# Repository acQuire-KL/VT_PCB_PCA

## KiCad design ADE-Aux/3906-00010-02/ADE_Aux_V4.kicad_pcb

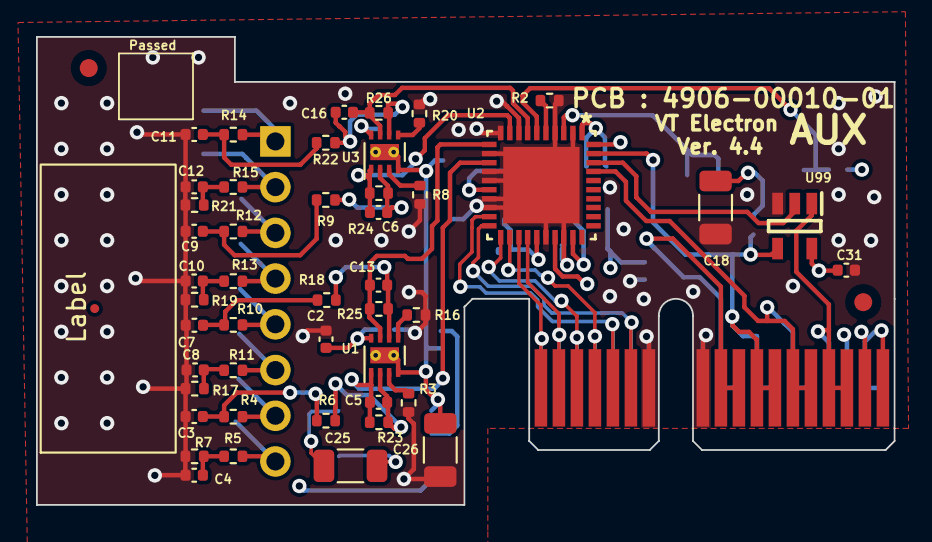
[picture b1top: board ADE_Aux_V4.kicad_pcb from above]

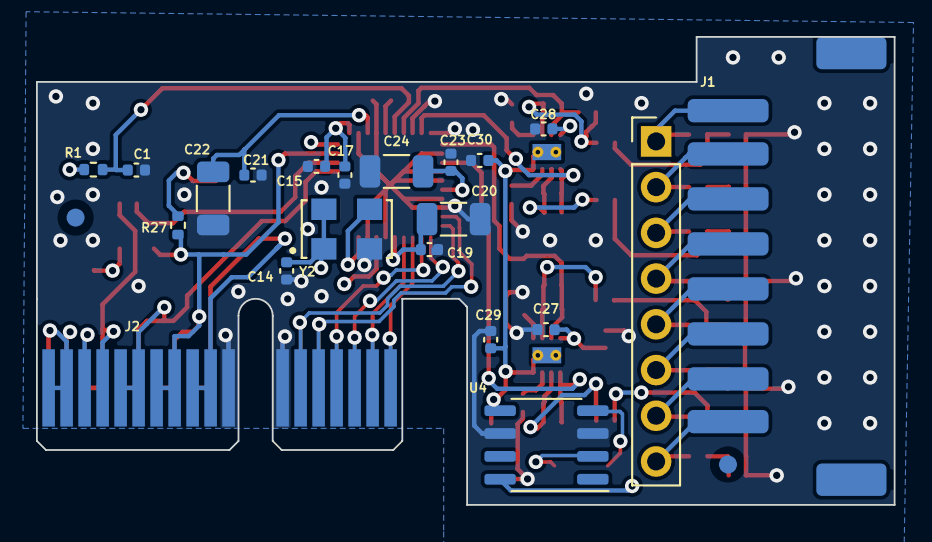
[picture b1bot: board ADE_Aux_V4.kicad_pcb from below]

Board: 4 copper layers, 47.6 x 26.0 mm, 72 parts (23 on the bottom side), 50 nets.

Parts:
C1, C3, C7, C9, C11: 22n; C_0402_1005Metric
C2, C5, C6, C13, C14, C15, C16, C17, C19, C21, C23, C27, C28, C29, C30, C31: 100n; C_0402_1005Metric
C4, C8, C10, C12: DNP; C_0402_1005Metric
C18, C20, C22, C24, C25, C26: 10u; C_1206_3216Metric
FID1, FID2, FID3, FID4: Fiducial; Fiducial_1mm_Mask2mm
J1: MUAS100-8-C-E; A2501-SR08-XH8AWB
J2: Bus_PCI_Express_x1_MOD; BUS_PCIexpress_x1
J15: MUAS100-8-C-E; PinHeader_1x08_P2.54mm_Vertical
R1, R2: 1k; R_0402_1005Metric
R3, R5, R7, R8, R11, R13, R15, R16, R17, R19, R20, R21: 0; R_0402_1005Metric
R4, R10, R12, R14: 100; R_0402_1005Metric
R6, R9, R18, R22, R27: 30K; R_0402_1005Metric
R23, R24, R25, R26: 137K; R_0402_1005Metric
TP1: Eticheta
U1, U3: TLV2186IDSGR; WSON-8-1EP_2x2mm_P0.5mm_EP0.9x1.6mm_ThermalVias
U2: ADE9430
U4: MC7660DR2; SO-8_3.9x4.9mm_P1.27mm
U99: NC7SZ126M5X; Buffer3S
Y2: ECS-5032MV-245.7-BN-TR; OSC_ECS-5032MV-245.7-BN-TR

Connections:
+3V3: C2.1, C14.1, C15.1, C17.1, C18.1, C27.2, C28.2, C31.2, J2.A1, J2.A2, J2.B1, J2.B2, R1.2, R27.1, U1.8 (V+), U2.1 (PullHigh), U2.27 (VDD), U3.8 (V+), U4.8 (V+), U99.5 (VCC), Y2.1 (TRI-STATE), Y2.4 (VDD)
/ADE_Reset: C1.1, J2.B3, R1.1, U2.6 (RESET)
/AVDDOUT: C19.1, C20.1, U2.25 (AVDDOUT)
/C+: C25.1, U4.2 (CAP+)
/C-: C25.2, U4.4 (CAP-)
/DVDDOUT: C21.1, C22.1, U2.3 (DVDDOUT)
/INP: C5.1, R23.1, U1.1, U2.13 (INP)
/IRP: C16.1, R26.1, U2.7 (IAP), U3.7
/ISP: C6.1, R24.1, U2.9 (IBP), U3.1
/ITP: C13.1, R25.1, U1.7, U2.11 (ICP)
/MISO: U2.38 (MISO), U99.2 (A)
/MOSI: J2.A7, J2.A8, J2.B7, J2.B8, R27.2, U2.39 (MOSI), U99.4 (Y)
/O_IN: U2.29 (CLKIN), Y2.3 (OUTPUT)
/PM1: R2.2, U2.5 (PM1)
/REF: C23.1, C24.1, U2.16 (REF)
/RN: C3.1, R4.1, R6.2
/RNM: J1.8, J15.8, R5.2
/RNP: J1.7, J15.7, R4.2
/RR: C11.1, R14.1, R22.2
/RRM: J1.2, J15.2, R15.2
/RRP: J1.1, J15.1, R14.2
/RS: C9.1, R9.2, R12.1
/RSM: J1.4, J15.4, R13.2
/RSP: J1.3, J15.3, R12.2
/RT: C7.1, R10.1, R18.2
/RTM: J1.6, J15.6, R11.2
/RTP: J1.5, J15.5, R10.2
/SCLK: J2.A5, J2.A6, J2.B5, J2.B6, U2.37 (SCLK)
/SS: J2.A9, J2.A10, J2.B9, J2.B10, U2.40 (SS)
/SYN: J2.A3, J2.A4, J2.B4, U99.1 (OE)
/UM: C26.2, C29.2, C30.2, U1.4 (V-), U1.9 (PAD), U3.4 (V-), U3.9 (PAD), U4.5 (VOUT)
/UR+: J2.A14, J2.B14, U2.19 (VAN)
/UR-: J2.A13, J2.B13, U2.20 (VAP)
/US+: J2.A16, J2.B16, U2.21 (VBN)
/US-: J2.A15, J2.B15, U2.22 (VBP)
/UT+: J2.A18, J2.B18, U2.23 (VCN)
/UT-: J2.A17, J2.B17, U2.24 (VCP)
GND: C1.2, C2.2, C3.2, C4.2, C7.2, C8.2, C9.2, C10.2, C11.2, C12.2, C14.2, C15.2, C17.2, C18.2, C19.2, C20.2, C21.2, C22.2, C23.2, C24.2, C26.1, C27.1, C28.1, C29.1, C30.1, C31.1, J2.A11, J2.A12, J2.B11, J2.B12, R2.1, R3.2, R7.2, R8.2, R16.2, R17.2, R19.2, R20.2, R21.2, U2.2 (DGND), U2.4 (PM0), U2.8 (IAN), U2.10 (IBN), U2.12 (ICN), U2.14 (INN), U2.15 (REFGND), U2.17 (NC1), U2.18 (NC2), U2.26 (AGND), U2.28 (GND), U2.41 (EP), U4.3 (GND), U4.6 (LV), U99.3 (GND), Y2.2 (GND)
unnamed: C4.1, R5.1, R7.1
unnamed: C8.1, R11.1, R17.1
unnamed: C10.1, R13.1, R19.1
unnamed: C12.1, R15.1, R21.1
unnamed: R3.1, U1.3 (+)
unnamed: C5.2, R6.1, R23.2, U1.2 (-)
unnamed: R16.1, U1.5 (+)
unnamed: C13.2, R18.1, R25.2, U1.6 (-)
unnamed: R8.1, U3.3 (+)
unnamed: C6.2, R9.1, R24.2, U3.2 (-)
unnamed: R20.1, U3.5 (+)
unnamed: C16.2, R22.1, R26.2, U3.6 (-)

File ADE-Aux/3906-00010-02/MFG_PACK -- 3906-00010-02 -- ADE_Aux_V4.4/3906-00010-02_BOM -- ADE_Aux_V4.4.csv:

"Reference","VTPN","Value","Datasheet","Footprint","Qty","DNP"
"FID1,FID2,FID3,FID4","4000-00000-00","Fiducial","~","Fiducial:Fiducial_1mm_Mask2mm","4","DNP"
"J2","4000-00000-00","Bus_PCI_Express_x1_MOD","http://www.ritrontek.com/uploadfile/2016/1026/20161026105231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","Connector_PCBEdge:BUS_PCIexpress_x1","1","DNP"
"J15","4000-00000-00","MUAS100-8-C-E","~","Connector_PinHeader_2.54mm:PinHeader_1x08_P2.54mm_Vertical","1","DNP"
"TP1","4000-00000-00","Eticheta","~","Symbol:Eticheta","1","DNP"
"C4,C8,C10,C12","4004-00000-00","DNP","~","Capacitor_SMD:C_0402_1005Metric","4",""
"R3,R5,R7,R8,R11,R13,R15,R16,R17,R19,R20,R21","4004-00001-00","0","~","Resistor_SMD:R_0402_1005Metric","12",""
"R1,R2","4004-00010-00","1k","~","Resistor_SMD:R_0402_1005Metric","2",""
"R4,R10,R12,R14","4004-00020-00","100","~","Resistor_SMD:R_0402_1005Metric","4",""
"R6,R9,R18,R22,R27","4004-00100-00","30K","~","Resistor_SMD:R_0402_1005Metric","5",""
"R23,R24,R25,R26","4004-02000-00","137K","~","Resistor_SMD:R_0402_1005Metric","4",""
"C1,C3,C7,C9,C11","4104-00020-00","22n","~","Capacitor_SMD:C_0402_1005Metric","5",""
"C2,C5,C6,C13,C14,C15,C16,C17,C19,C21,C23,C27,C28,C29,C30,C31","4104-00100-00","100n","~","Capacitor_SMD:C_0402_1005Metric","16",""
"C18,C20,C22,C24,C25,C26","4112-00100-00","10u","~","Capacitor_SMD:C_1206_3216Metric","6",""
"J1","4408-00010-00","MUAS100-8-C-E","~","Connector_JST:A2501-SR08-XH8AWB","1",""
"U4","4520-00030-00","MC7660DR2","http://www.ti.com/lit/ds/symlink/lmc7660.pdf","Package_SO:SO-8_3.9x4.9mm_P1.27mm","1",""
"U2","4706-00030-00","ADE9430","","Package_QFP:ADE9430","1",""
"U1,U3","4708-00010-00","TLV2186IDSGR","-- mixed values --","Package_SON:WSON-8-1EP_2x2mm_P0.5mm_EP0.9x1.6mm_ThermalVias","2",""
"Y2","4712-00020-00","ECS-5032MV-245.7-BN-TR","","Oscillator:OSC_ECS-5032MV-245.7-BN-TR","1",""
"U99","4726-00010-00","NC7SZ126M5X","","Buffer3S:Buffer3S","1",""

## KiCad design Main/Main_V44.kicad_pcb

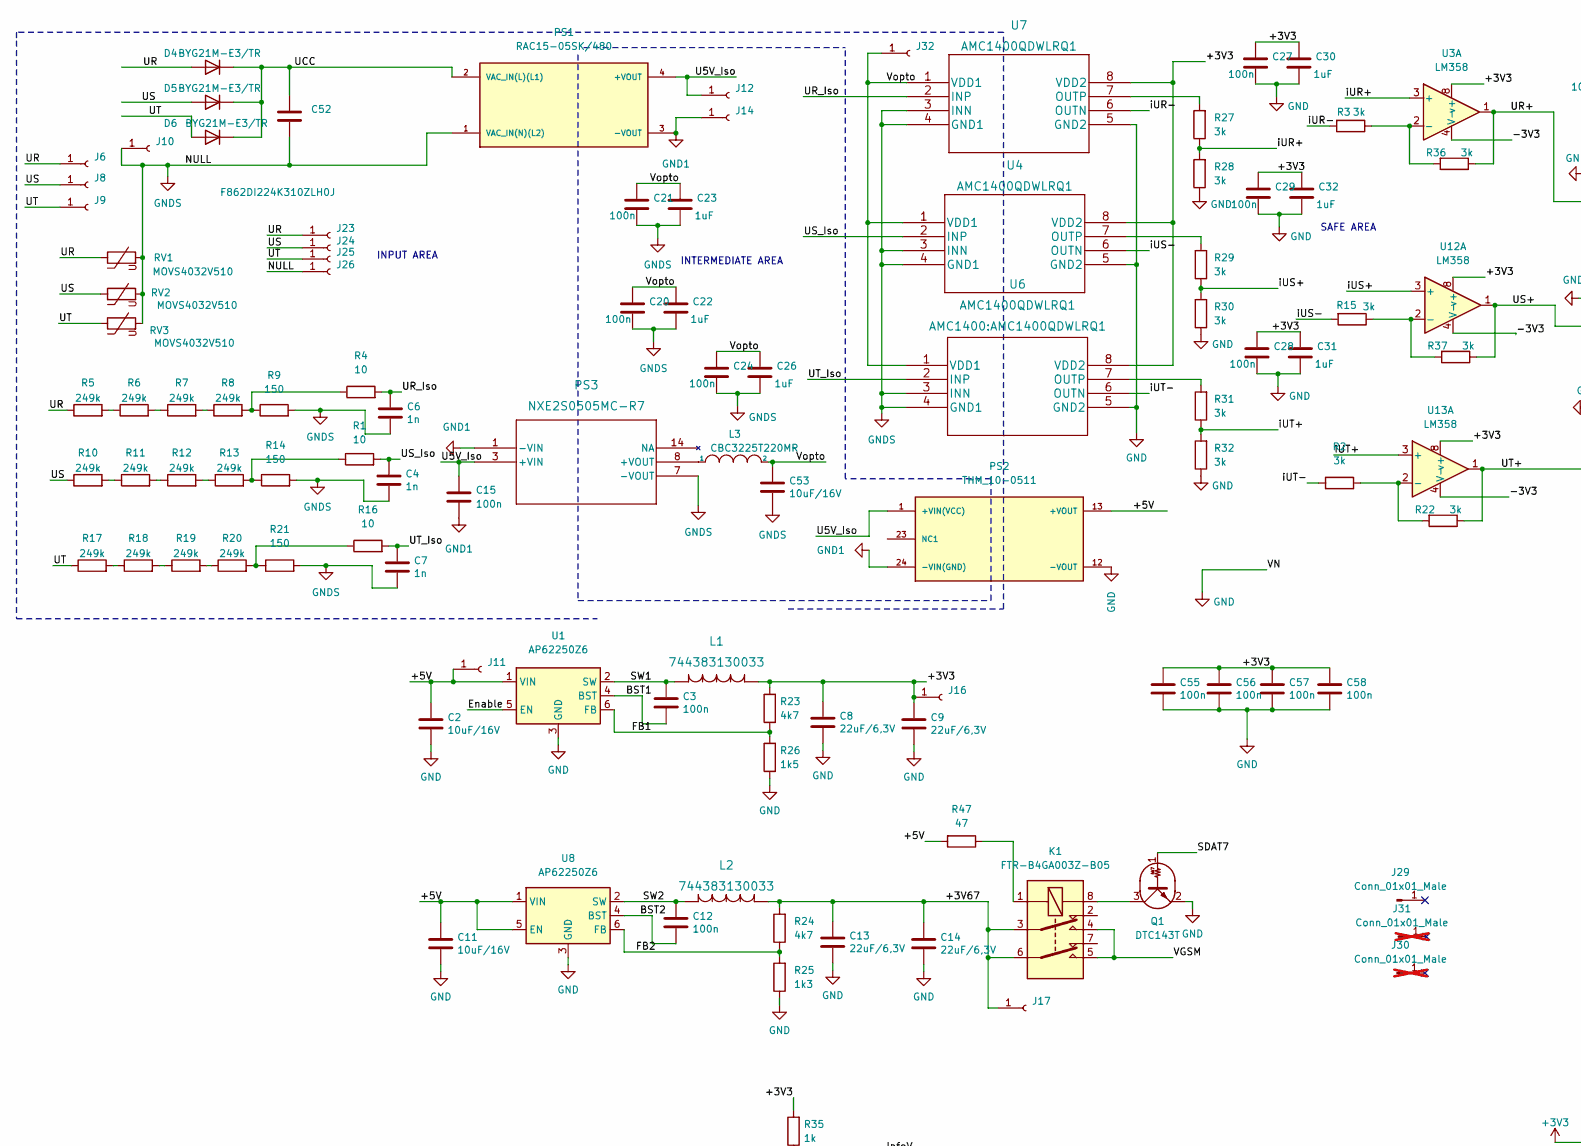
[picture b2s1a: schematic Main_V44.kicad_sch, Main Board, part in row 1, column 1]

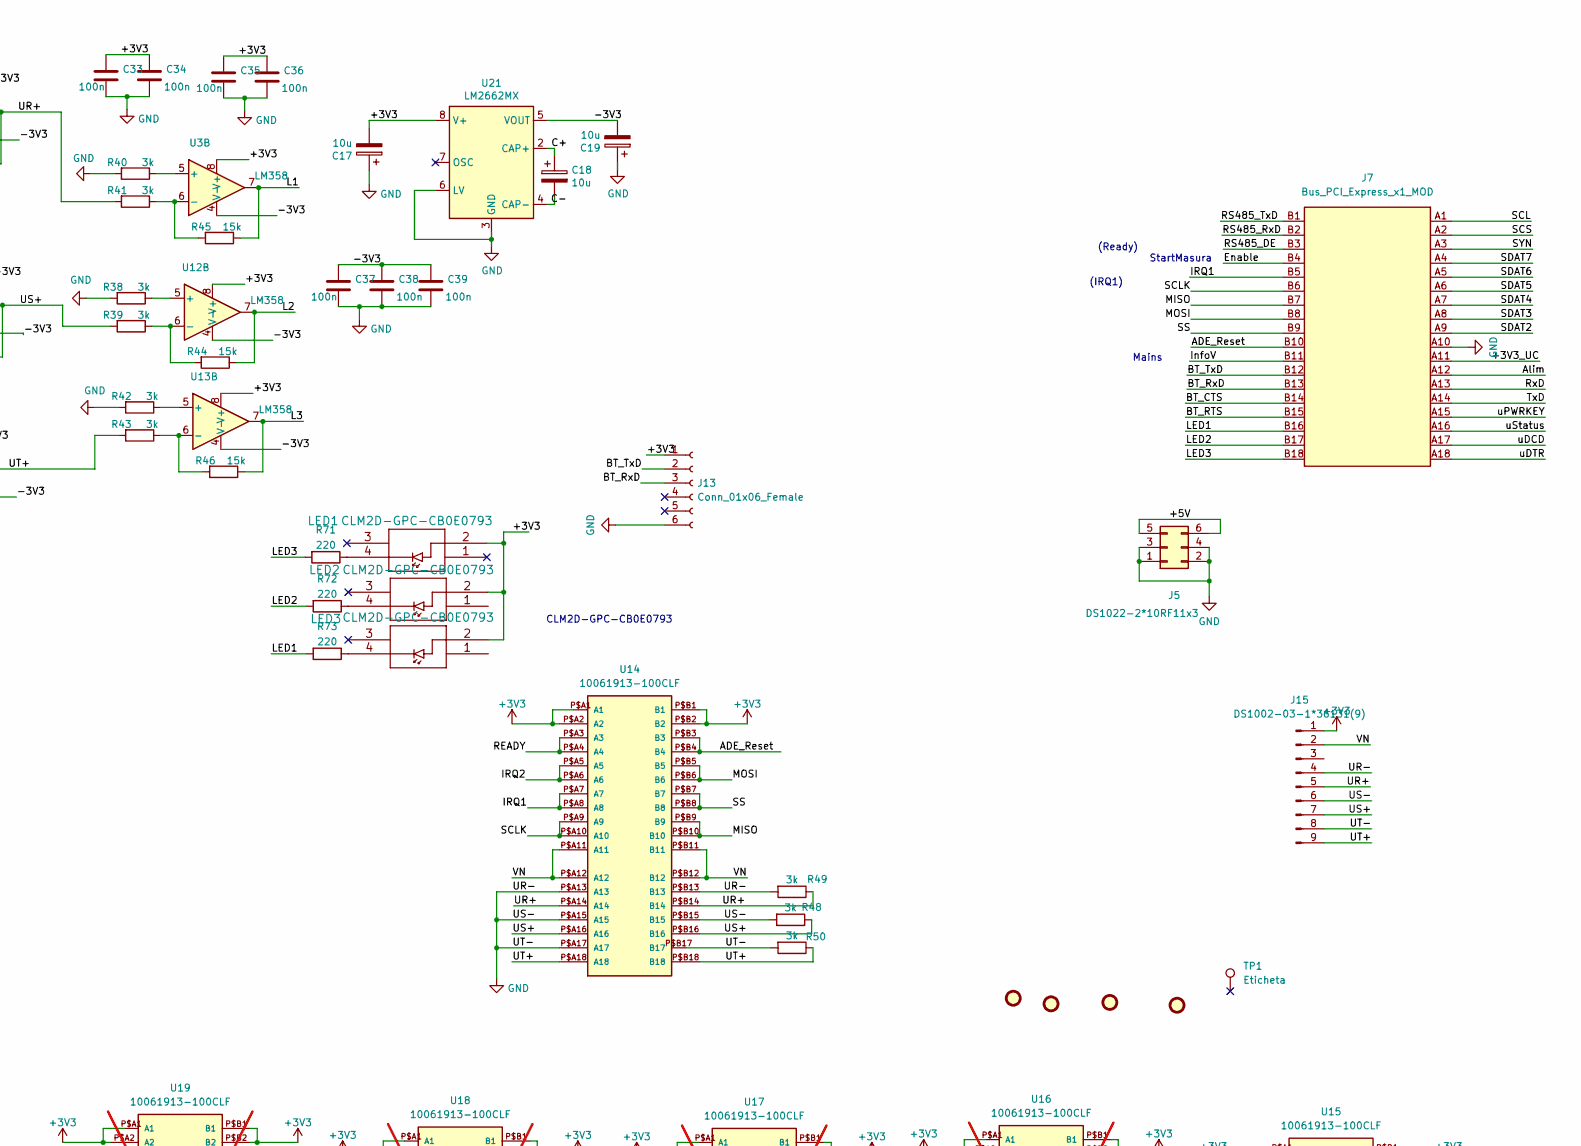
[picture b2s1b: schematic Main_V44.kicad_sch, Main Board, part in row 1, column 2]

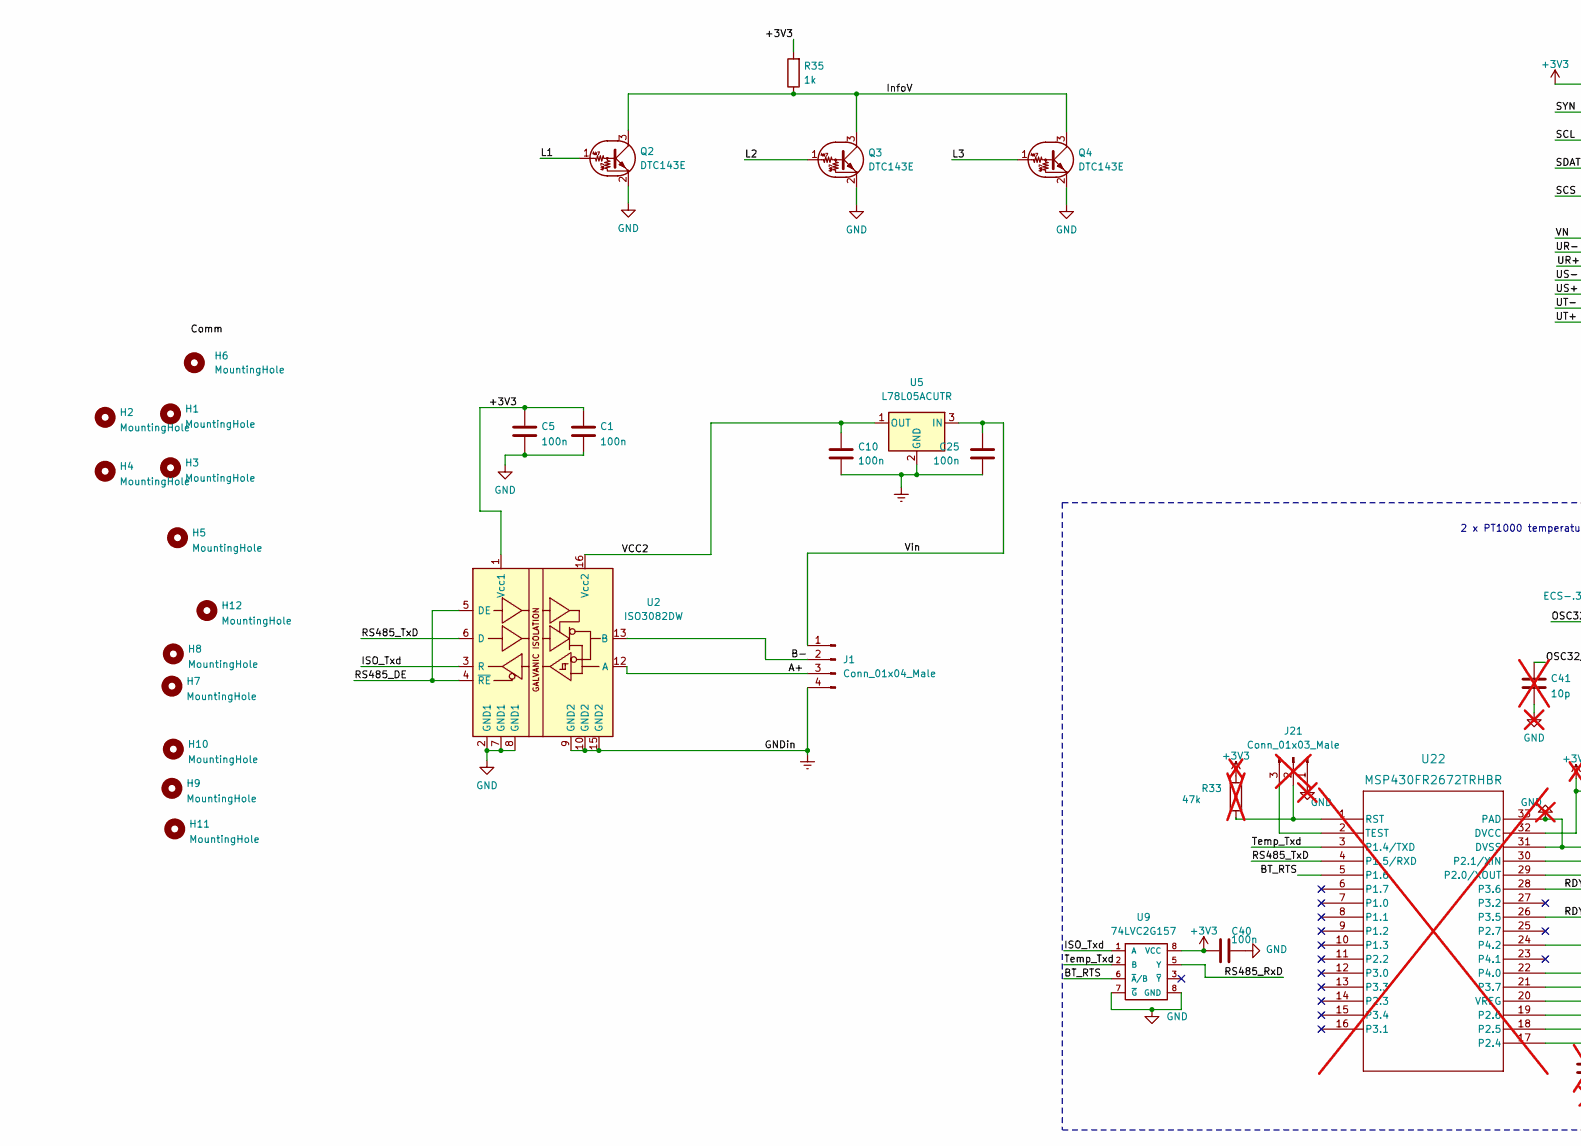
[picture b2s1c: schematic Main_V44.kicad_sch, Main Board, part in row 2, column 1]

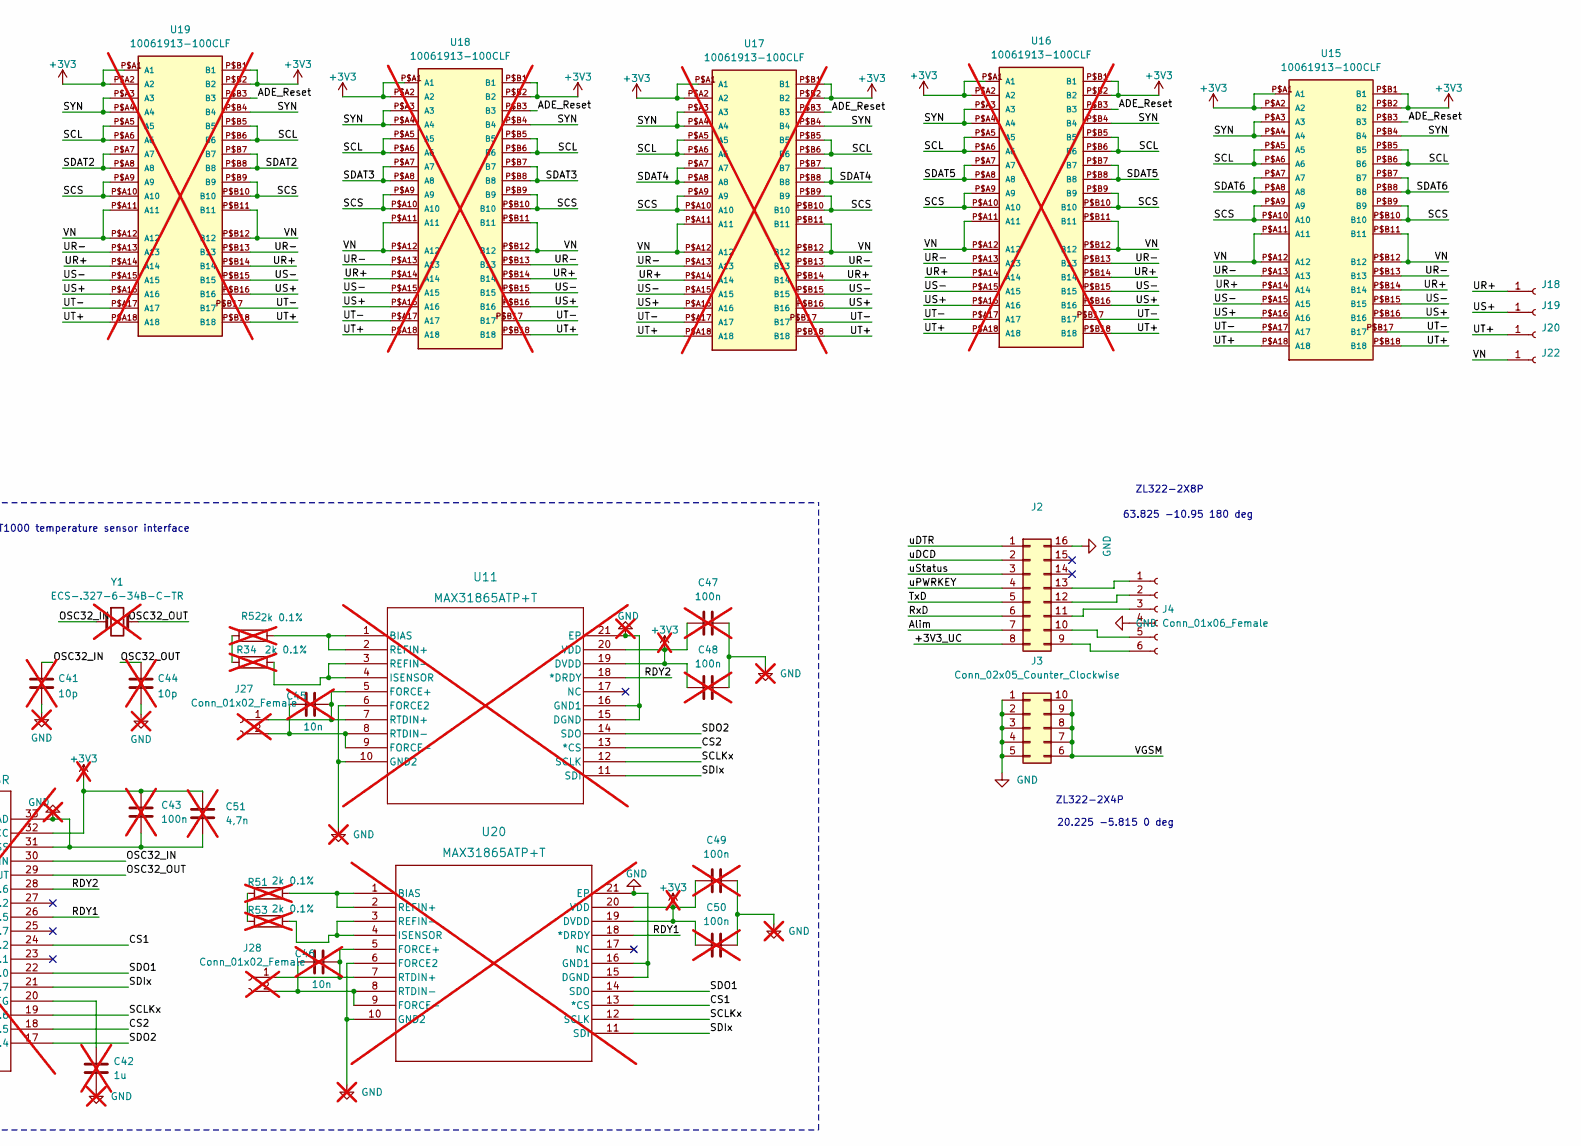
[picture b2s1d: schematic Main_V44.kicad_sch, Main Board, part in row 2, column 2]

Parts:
C1, C3, C5, C10, C12, C15, C20, C21, C24, C25, C27, C28, C29, C33, C34, C35, C36, C37, C38, C39, C40, C55, C56, C57, C58: 100n; C_0603_1608Metric
C2, C11, C53: 10uF/16V; C_1206_3216Metric
C4, C6, C7: 1n; C_0603_1608Metric
C8, C9, C13, C14: 22uF/6,3V; C_1206_3216Metric
C17, C18, C19: 10u; C_1206_3216Metric
C22, C23, C26, C30, C31, C32: 1uF; C_0603_1608Metric
C41, C44: 10p; C_0603_1608Metric; not fitted
C42: 1u; C_0603_1608Metric; not fitted
C43, C47, C48, C49, C50: 100n; C_0603_1608Metric; not fitted
C45, C46: 10n; C_0603_1608Metric; not fitted
C51: 4,7n; C_0603_1608Metric; not fitted
C52: F862DI224K310ZLH0J; C_Rect_L24.0mm_W7.0mm_P22.50mm_MKT
D4, D5, D6: BYG21M-E3/TR; D_SMA
FID1, FID2, FID3, FID4: Fiducial; Fiducial_1mm_Mask2mm
H1, H6: MountingHole; MountingHole_3.2mm_M3_ISO14580_Pad_TopBottom
H2, H3, H4, H5, H7, H8, H9, H10, H11, H12: MountingHole; MountingHole_3.2mm_M3
J1: Conn_01x04_Male; A2501-SR04-XH4AWB
J2: Conn_02x08_Counter_Clockwise; PinSocket_2x08_P2.54mm_Vertical_SMD_MOD
J3: Conn_02x05_Counter_Clockwise; PinSocket_2x05_P2.54mm_Vertical_SMD
J4, J13: Conn_01x06_Female; PinSocket_1x06_P2.54mm_Vertical
J5: DS1022-2*10RF11x3; PinHeader_2x03_P2.54mm_Horizontal
J6, J8, J9, J10, J11, J12, J14, J16, J17, J18, J19, J20, J22, J32: Conn_01x01_Female; TestPoint_DELTA
J7: Bus_PCI_Express_x1_MOD; BUS_PCIexpress_x1
J15: DS1002-03-1*36131(9); PinSocket_1x09_P2.54mm_Vertical
J21: Conn_01x03_Male; PinHeader_1x03_P2.54mm_Vertical; not fitted
J23: Conn_01x01_Female; DELTA_SolderWire-1.5sqmm_1x01_D1.7mm_OD3.9mm
J24, J25, J26: Conn_01x01_Female; DELTA_R_SolderWire-1.5sqmm_1x01_D1.7mm_OD3.9mm
J27, J28: Conn_01x02_Female; TerminalBlock_bornier-2_P5.08mm; not fitted
J29: Conn_01x01_Male; TestPoint_Pad_5.1x5.1mm
J30, J31: Conn_01x01_Male; TestPoint_Pad_5.1x5.1mm; not fitted
K1: FTR-B4GA003Z-B05; Relay_Fujitsu_FTR-B4GA003
L1, L2: 744383130033
L3: CBC3225T220MR; L_1206_3216Metric
LED1, LED2, LED3: CLM2D-GPC-CB0E0793
PS1: RAC15-05SK/480; CONV_RAC15-12SK_480; PARTREV 0/2022
PS2: THM_10-0511; CONV_THM_10-0511; PARTREV Jan 06, 2021
PS3: NXE2S0505MC-R7; NXE2_SINGLE_SURFACE_MUR
Q1: DTC143T; SOT-23
Q2, Q3, Q4: DTC143E; SOT-23
R1, R4, R16: 10; R_0603_1608Metric
R2, R3, R15, R22, R27, R28, R29, R30, R31, R32, R36, R37, R38, R39, R40, R41, R42, R43, R48, R49, R50: 3k; R_0603_1608Metric
R5, R6, R7, R8, R10, R11, R12, R13, R17, R18, R19, R20: 249k; R_2512_6332Metric
R9, R14, R21: 150; R_0603_1608Metric
R23, R24: 4k7; R_0603_1608Metric
R25: 1k3; R_0603_1608Metric
R26: 1k5; R_0603_1608Metric
R33: 47k; R_0603_1608Metric; not fitted
R34, R51, R52, R53: 2k 0.1%; R_0603_1608Metric; not fitted
R35: 1k; R_0603_1608Metric
R44, R45, R46: 15k; R_0603_1608Metric
R47: 47; R_0603_1608Metric
R71, R72, R73: 220; R_0603_1608Metric
RV1, RV2, RV3: MOVS4032V510; MOVS4032V460
TP1: Eticheta
U1, U8: AP62250Z6; SOT-563
U2: ISO3082DW; SOIC-16W_7.5x10.3mm_P1.27mm
U3, U12, U13: LM358; SO-8_3.9x4.9mm_P1.27mm
U4, U6, U7: AMC1400QDWLRQ1
U5: L78L05ACUTR; SOT-89-3
U9: 74LVC2G157; VSSOP-8_2.4x2.1mm_P0.5mm
U11, U20: MAX31865ATP+T; 21-0140L_T2055-5_MXM; not fitted
U14, U15: 10061913-100CLF; MPN 10061913-100CLF
U16, U17, U18, U19: 10061913-100CLF; MPN 10061913-100CLF; not fitted
U21: LM2662MX; SO-8_3.9x4.9mm_P1.27mm
U22: MSP430FR2672TRHBR; VQFN32_5X5_TEX; not fitted
Y1: ECS-.327-6-34B-C-TR; Crystal_SMD_EuroQuartz_EQ161-2Pin_3.2x1.5mm; not fitted

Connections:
/+3V3_UC: J2.8, J7.A11
/+3V67: C13.1, C14.1, J17.1, K1.3, K1.6, L2.1, R24.2
/+5V: C2.1, C11.1, J5.5, J5.6, J11.1, PS2.13 (+VOUT), R47.2, U1.1 (VIN), U8.1 (VIN), U8.5 (EN)
/-3V3: C19.2, C37.1, C38.1, C39.1, U3.4 (V-), U12.4 (V-), U13.4 (V-), U21.5 (VOUT)
/A+: J1.3, U2.12 (A)
/ADE_Reset: J7.B10, U14.P$B3 (B3), U14.P$B4 (B4), U15.P$B3 (B3), U16.P$B3 (B3), U17.P$B3 (B3), U18.P$B3 (B3), U19.P$B3 (B3)
/Alim: J2.7, J7.A12
/B-: J1.2, U2.13 (B)
/BST1: C3.2, U1.4 (BST)
/BST2: C12.2, U8.4 (BST)
/BT_CTS: J7.B14
/BT_RTS: J7.B15, U9.6 (~A/B), U22.5 (P1.6)
/BT_RxD: J7.B13, J13.3
/BT_TxD: J7.B12, J13.2
/C+: C18.1, U21.2 (CAP+)
/C-: C18.2, U21.4 (CAP-)
/CS1: U20.13 (*CS), U22.24 (P4.2)
/CS2: U11.13 (*CS), U22.18 (P2.5)
/Enable: J7.B4, U1.5 (EN)
/FB1: R23.1, R26.2, U1.6 (FB)
/FB2: R24.1, R25.2, U8.6 (FB)
/IRQ1: J7.B5, U14.P$A7 (A7), U14.P$A8 (A8)
/IRQ2: U14.P$A5 (A5), U14.P$A6 (A6)
/ISO_Txd: U2.3 (R), U9.1 (A)
/InfoV: J7.B11, Q2.3 (C), Q3.3 (C), Q4.3 (C), R35.1
/L1: Q2.1 (B), R45.1, U3.7
/L2: Q3.1 (B), R44.1, U12.7
/L3: Q4.1 (B), R46.1, U13.7
/LED1: J7.B16, R73.2
/LED2: J7.B17, R72.2
/LED3: J7.B18, R71.2
/MISO: J7.B7, U14.P$B9 (B9), U14.P$B10 (B10)
/MOSI: J7.B8, U14.P$B5 (B5), U14.P$B6 (B6)
/OSC32_IN: C41.1, U22.30 (P2.1/XIN), Y1.1
/OSC32_OUT: C44.1, U22.29 (P2.0/XOUT), Y1.2
/RDY1: U20.18 (*DRDY), U22.26 (P3.5)
/RDY2: U11.18 (*DRDY), U22.28 (P3.6)
/READY: U14.P$A3 (A3), U14.P$A4 (A4)
/RS485_DE: J7.B3, U2.4 (~RE), U2.5 (DE)
/RS485_RxD: J7.B2, U9.5 (Y)
/RS485_TxD: J7.B1, U2.6 (D), U22.4 (P1.5/RXD)
/RxD: J2.6, J7.A13
/SCL: J7.A1, U15.P$A5 (A5), U15.P$A6 (A6), U15.P$B5 (B5), U15.P$B6 (B6), U16.P$A5 (A5), U16.P$A6 (A6), U16.P$B5 (B5), U16.P$B6 (B6), U17.P$A5 (A5), U17.P$A6 (A6), U17.P$B5 (B5), U17.P$B6 (B6), U18.P$A5 (A5), U18.P$A6 (A6), U18.P$B5 (B5), U18.P$B6 (B6), U19.P$A5 (A5), U19.P$A6 (A6), U19.P$B5 (B5), U19.P$B6 (B6)
/SCLK: J7.B6, U14.P$A9 (A9), U14.P$A10 (A10)
/SCLKx: U11.12 (SCLK), U20.12 (SCLK), U22.19 (P2.6)
/SCS: J7.A2, U15.P$A9 (A9), U15.P$A10 (A10), U15.P$B9 (B9), U15.P$B10 (B10), U16.P$A9 (A9), U16.P$A10 (A10), U16.P$B9 (B9), U16.P$B10 (B10), U17.P$A9 (A9), U17.P$A10 (A10), U17.P$B9 (B9), U17.P$B10 (B10), U18.P$A9 (A9), U18.P$A10 (A10), U18.P$B9 (B9), U18.P$B10 (B10), U19.P$A9 (A9), U19.P$A10 (A10), U19.P$B9 (B9), U19.P$B10 (B10)
/SDAT2: J7.A9, U19.P$A7 (A7), U19.P$A8 (A8), U19.P$B7 (B7), U19.P$B8 (B8)
/SDAT3: J7.A8, U18.P$A7 (A7), U18.P$A8 (A8), U18.P$B7 (B7), U18.P$B8 (B8)
/SDAT4: J7.A7, U17.P$A7 (A7), U17.P$A8 (A8), U17.P$B7 (B7), U17.P$B8 (B8)
/SDAT5: J7.A6, U16.P$A7 (A7), U16.P$A8 (A8), U16.P$B7 (B7), U16.P$B8 (B8)
/SDAT6: J7.A5, U15.P$A7 (A7), U15.P$A8 (A8), U15.P$B7 (B7), U15.P$B8 (B8)
/SDAT7: J7.A4, Q1.1 (B)
/SDIx: U11.11 (SDI), U20.11 (SDI), U22.21 (P3.7)
/SDO1: U20.14 (SDO), U22.22 (P4.0)
/SDO2: U11.14 (SDO), U22.17 (P2.4)
/SS: J7.B9, U14.P$B7 (B7), U14.P$B8 (B8)
/SW1: C3.1, L1.2, U1.2 (SW)
/SW2: C12.1, L2.2, U8.2 (SW)
/SYN: J7.A3, U15.P$A3 (A3), U15.P$A4 (A4), U15.P$B4 (B4), U16.P$A3 (A3), U16.P$A4 (A4), U16.P$B4 (B4), U17.P$A3 (A3), U17.P$A4 (A4), U17.P$B4 (B4), U18.P$A3 (A3), U18.P$A4 (A4), U18.P$B4 (B4), U19.P$A3 (A3), U19.P$A4 (A4), U19.P$B4 (B4)
/Temp_Txd: U9.2 (B), U22.3 (P1.4/TXD)
/TxD: J2.5, J7.A14
/U5V_Iso: C15.1, J12.1, PS1.4 (+VOUT), PS2.1 (+VIN(VCC)), PS3.3 (+VIN)
/UCC: C52.1, D4.1 (K), D5.1 (K), D6.1 (K), PS1.2 (VAC_IN(L)(L1))
/UR: D4.2 (A), J6.1, J23.1, R5.1, RV1.1
/UR+: J15.5, J18.1, R36.1, R41.2, R49.1, U3.1, U14.P$A14 (A14), U14.P$B14 (B14), U15.P$A14 (A14), U15.P$B14 (B14), U16.P$A14 (A14), U16.P$B14 (B14), U17.P$A14 (A14), U17.P$B14 (B14), U18.P$A14 (A14), U18.P$B14 (B14), U19.P$A14 (A14), U19.P$B14 (B14)
/UR_Iso: C6.1, R4.2, U7.2 (INP)
/US: D5.2 (A), J8.1, J24.1, R10.1, RV2.1
/US+: J15.7, J19.1, R37.1, R39.2, R48.1, U12.1, U14.P$A16 (A16), U14.P$B16 (B16), U15.P$A16 (A16), U15.P$B16 (B16), U16.P$A16 (A16), U16.P$B16 (B16), U17.P$A16 (A16), U17.P$B16 (B16), U18.P$A16 (A16), U18.P$B16 (B16), U19.P$A16 (A16), U19.P$B16 (B16)
/US_Iso: C4.1, R1.2, U4.2 (INP)
/UT: D6.2 (A), J9.1, J25.1, R17.1, RV3.1
/UT+: J15.9, J20.1, R22.1, R43.2, R50.1, U13.1, U14.P$A18 (A18), U14.P$B18 (B18), U15.P$A18 (A18), U15.P$B18 (B18), U16.P$A18 (A18), U16.P$B18 (B18), U17.P$A18 (A18), U17.P$B18 (B18), U18.P$A18 (A18), U18.P$B18 (B18), U19.P$A18 (A18), U19.P$B18 (B18)
/UT_Iso: C7.1, R16.2, U6.2 (INP)
/VCC2: C10.1, U2.16 (Vcc2), U5.1 (OUT)
/VGSM: J3.6, J3.7, J3.8, J3.9, J3.10, K1.4, K1.5
/Vin: C25.1, J1.1, U5.3 (IN)
/Vopto: C20.1, C21.1, C22.1, C23.1, C24.1, C26.1, C53.1, J32.1, L3.2, U4.1 (VDD1), U6.1 (VDD1), U7.1 (VDD1)
/iUR+: R27.1, R28.2, U3.3 (+)
/iUR-: R3.2, U7.6 (OUTN)
/iUS+: R29.1, R30.2, U12.3 (+)
/iUS-: R15.2, U4.6 (OUTN)
/iUT+: R31.1, R32.2, U13.3 (+)
/iUT-: R2.2, U6.6 (OUTN)
/uDCD: J2.2, J7.A17
/uDTR: J2.1, J7.A18
/uPWRKEY: J2.4, J7.A15
/uStatus: J2.3, J7.A16
Earth: C10.2, C25.2, J1.4, U2.9 (GND2), U2.10 (GND2), U2.15 (GND2), U5.2 (GND)
GND1: C15.2, J14.1, PS1.3 (-VOUT), PS2.24 (-VIN(GND)), PS3.1 (-VIN)
GNDS: C4.2, C6.2, C7.2, C20.2, C21.2, C22.2, C23.2, C24.2, C26.2, C52.2, C53.2, J10.1, J26.1, PS1.1 (VAC_IN(N)(L2)), PS3.7 (-VOUT), R9.2, R14.2, R21.2, RV1.2, RV2.2, RV3.2, U4.3 (INN), U4.4 (GND1), U6.3 (INN), U6.4 (GND1), U7.3 (INN), U7.4 (GND1)
unnamed: J2.9, J4.6
unnamed: J2.10, J4.5
unnamed: J2.11, J4.3
unnamed: J2.12, J4.2
unnamed: J2.13, J4.1
unnamed: J21.2, R33.1, U22.1 (RST)
unnamed: J21.3, U22.2 (TEST)
unnamed: C45.2, J27.1, U11.5 (FORCE+), U11.7 (RTDIN+)
unnamed: C45.1, J27.2, U11.8 (RTDIN-), U11.9 (FORCE-)
unnamed: C46.2, J28.1, U20.5 (FORCE+), U20.7 (RTDIN+)
unnamed: C46.1, J28.2, U20.8 (RTDIN-), U20.9 (FORCE-)
unnamed: K1.1, R47.1
unnamed: LED1.4, R71.1
unnamed: LED2.4, R72.1
unnamed: LED3.4, R73.1
unnamed: L3.1, PS3.8 (+VOUT)
unnamed: K1.8, Q1.3 (C)
unnamed: R1.1, R13.2, R14.1
unnamed: R4.1, R8.2, R9.1
unnamed: R5.2, R6.1
unnamed: R6.2, R7.1
unnamed: R7.2, R8.1
unnamed: R10.2, R11.1
unnamed: R11.2, R12.1
unnamed: R12.2, R13.1
unnamed: R16.1, R20.2, R21.1
unnamed: R17.2, R18.1
unnamed: R18.2, R19.1
unnamed: R19.2, R20.1
unnamed: R34.2, R52.1
unnamed: R51.2, R53.2
unnamed: R3.1, R36.2, U3.2 (-)
unnamed: R40.1, U3.5 (+)
unnamed: R41.1, R45.2, U3.6 (-)
unnamed: R29.2, U4.7 (OUTP)
unnamed: R31.2, U6.7 (OUTP)
unnamed: R27.2, U7.7 (OUTP)
unnamed: R52.2, U11.1 (BIAS), U11.2 (REFIN+)
unnamed: R34.1, U11.3 (REFIN-), U11.4 (ISENSOR)
unnamed: R15.1, R37.2, U12.2 (-)
unnamed: R38.1, U12.5 (+)
unnamed: R39.1, R44.2, U12.6 (-)
unnamed: R2.1, R22.2, U13.2 (-)
unnamed: R42.1, U13.5 (+)
unnamed: R43.1, R46.2, U13.6 (-)
unnamed: R51.1, U20.1 (BIAS), U20.2 (REFIN+)
unnamed: R53.1, U20.3 (REFIN-), U20.4 (ISENSOR)
unnamed: C42.2, U22.20 (VREG)

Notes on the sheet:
ZL322-2X4P
ZL322-2X8P
20.225 -5.815 0 deg
(Ready)
2 x PT1000 temperature sensor interface
Mains
(IRQ1)
CLM2D-GPC-CB0E0793
StartMasura
63.825 -10.95 180 deg
SAFE AREA
INPUT AREA
INTERMEDIATE AREA

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
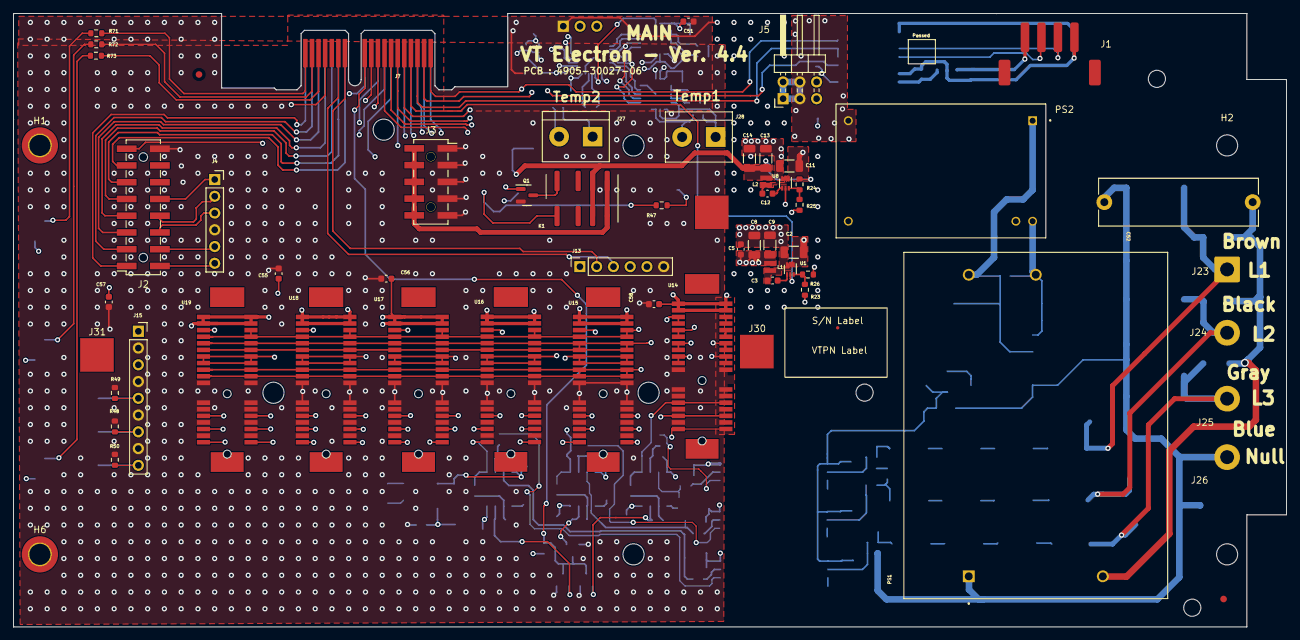
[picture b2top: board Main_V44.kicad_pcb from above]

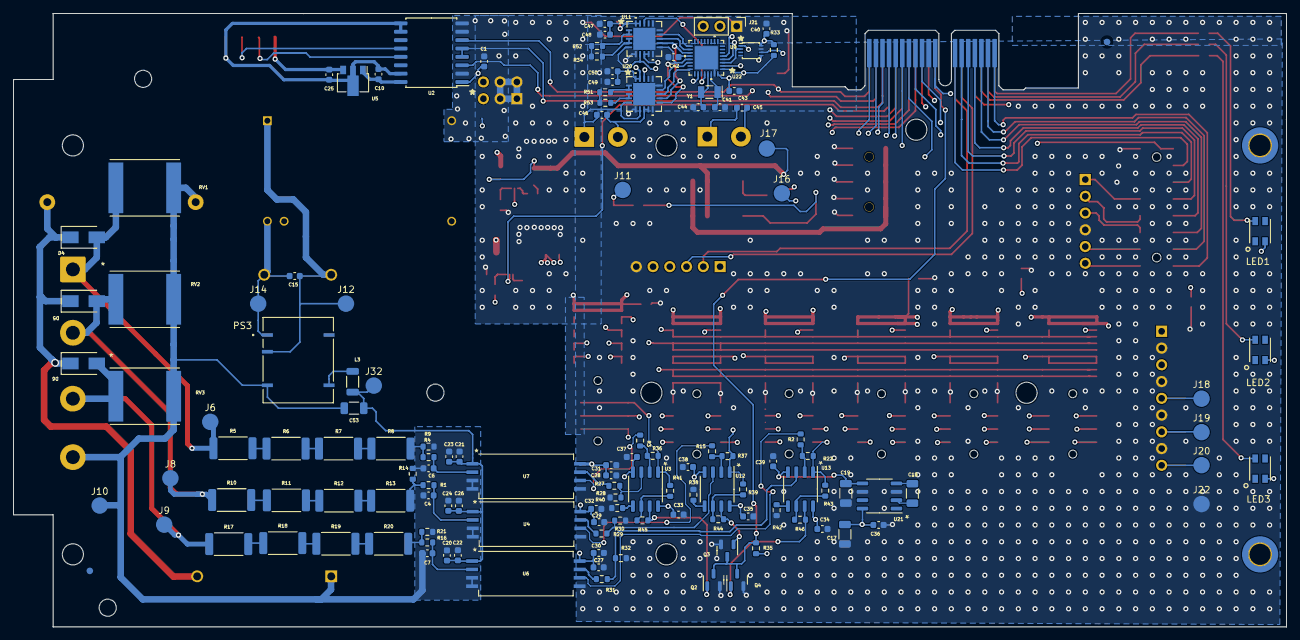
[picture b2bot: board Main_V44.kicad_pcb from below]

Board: 4 copper layers, 193.0 x 93.0 mm, 203 parts (131 on the bottom side), 138 nets.

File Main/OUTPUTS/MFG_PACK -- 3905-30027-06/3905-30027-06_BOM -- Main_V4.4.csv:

"Reference","Value","Datasheet","Footprint","Qty","DNP","VTPN"
"C1,C3,C5,C10,C12,C15,C20,C21,C24,C25,C27,C28,C29,C33,C34,C35,C36,C37,C38,C39,C40,C55,C56,C57,C58","100n","~","Capacitor_SMD:C_0603_1608Metric","25","","4106-00020-00"
"C2,C11,C53","10uF/16V","~","Capacitor_SMD:C_1206_3216Metric","3","","4112-00110-00"
"C4,C6,C7","1n","~","Capacitor_SMD:C_0603_1608Metric","3","","4106-00030-00"
"C8,C9,C13,C14","22uF/6,3V","~","Capacitor_SMD:C_1206_3216Metric","4","","4112-00150-00"
"C17,C18,C19","10u","~","Capacitor_SMD:C_1206_3216Metric","3","","4112-00100-00"
"C22,C23,C26,C30,C31,C32","1uF","~","Capacitor_SMD:C_0603_1608Metric","6","","4106-00100-00"
"C41,C44","10p","~","Capacitor_SMD:C_0603_1608Metric","2","DNP","4106-00010-00"
"C42","1u","~","Capacitor_SMD:C_0603_1608Metric","1","DNP","4106-00100-00"
"C43,C47,C48,C49,C50","100n","~","Capacitor_SMD:C_0603_1608Metric","5","DNP","4106-00020-00"
"C45,C46","10n","~","Capacitor_SMD:C_0603_1608Metric","2","DNP","4106-00015-00"
"C51","4,7n","~","Capacitor_SMD:C_0603_1608Metric","1","DNP","4106-00050-00"
"C52","F862DI224K310ZLH0J","~","Capacitor_THT:C_Rect_L24.0mm_W7.0mm_P22.50mm_MKT","1","","4130-00010-00"
"D4,D5,D6","BYG21M-E3/TR","~","Diode_SMD:D_SMA","3","","4510-00010-00"
"FID1,FID2,FID3,FID4","Fiducial","~","Fiducial:Fiducial_1mm_Mask2mm","4","","4000-00000-00"
"H1,H2,H3,H4,H5,H6,H7,H8,H9,H10,H11,H12","MountingHole","~","-- mixed values --","12","","4000-00000-00"
"J1","Conn_01x04_Male","~","Connector_JST:A2501-SR04-XH4AWB","1","","4408-00030-00"
"J2","Conn_02x08_Counter_Clockwise","~","Connector_PinSocket_2.54mm:PinSocket_2x08_P2.54mm_Vertical_SMD_MOD","1","","4402-10021-00"
"J3","Conn_02x05_Counter_Clockwise","~","Connector_PinSocket_2.54mm:PinSocket_2x05_P2.54mm_Vertical_SMD","1","","4402-10011-00"
"J4,J13","Conn_01x06_Female","~","Connector_PinSocket_2.54mm:PinSocket_1x06_P2.54mm_Vertical","2","","4401-00050-00"
"J5","DS1022-2*10RF11x3","~","Connector_PinHeader_2.54mm:PinHeader_2x03_P2.54mm_Horizontal","1","","4400-00015-00"
"J6,J8,J9,J10,J11,J12,J14,J16,J17,J18,J19,J20,J22,J23,J24,J25,J26,J32","Conn_01x01_Female","~","-- mixed values --","18","","4000-00000-00"
"J7","Bus_PCI_Express_x1_MOD","http://www.ritrontek.com/uploadfile/2016/1026/20161026105231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","Connector_PCBEdge:BUS_PCIexpress_x1","1","","4000-00000-00"
"J15","DS1002-03-1*36131(9)","~","Connector_PinSocket_2.54mm:PinSocket_1x09_P2.54mm_Vertical","1","","4412-00050-00"
"J21","Conn_01x03_Male","~","Connector_PinHeader_2.54mm:PinHeader_1x03_P2.54mm_Vertical","1","DNP","4401-00040-00"
"J27,J28","Conn_01x02_Female","~","TerminalBlock:TerminalBlock_bornier-2_P5.08mm","2","DNP","4420-20010-00"
"J29","Conn_01x01_Male","~","TestPoint:TestPoint_Pad_5.1x5.1mm","1","","4753-00010-00"
"J30,J31","Conn_01x01_Male","~","TestPoint:TestPoint_Pad_5.1x5.1mm","2","DNP","4753-00010-00"
"K1","FTR-B4GA003Z-B05","https://www.fujitsu.com/downloads/MICRO/fcai/relays/ftr-f1.pdf","Relay_SMD:Relay_Fujitsu_FTR-B4GA003","1","","4750-00010-00"
"L1,L2","744383130033","","Inductanta744:744383130033","2","","4300-00010-00"
"L3","CBC3225T220MR","~","Inductor_SMD:L_1206_3216Metric","1","","4300-00020-00"
"LED1,LED2,LED3","CLM2D-GPC-CB0E0793","","LedSMD_Cree:CLM2D-GPC-CB0E0793","3","","4752-00010-00"
"PS1","RAC15-05SK/480","","RAC15:CONV_RAC15-12SK_480","1","","4520-30010-00"
"PS2","THM_10-0511","","THM 10-0511:CONV_THM_10-0511","1","","4520-20010-00"
"PS3","NXE2S0505MC-R7","NXE2S0505MC-R7","NXE2S0505MC-R7:NXE2_SINGLE_SURFACE_MUR","1","","4520-20022-00"
"Q1","DTC143T","","Package_TO_SOT_SMD:SOT-23","1","","4500-00020-00"
"Q2,Q3,Q4","DTC143E","","Package_TO_SOT_SMD:SOT-23","3","","4500-00030-00"
"R1,R4,R16","10","~","Resistor_SMD:R_0603_1608Metric","3","","4006-00030-00"
"R2,R3,R15,R22,R27,R28,R29,R30,R31,R32,R36,R37,R38,R39,R40,R41,R42,R43,R48,R49,R50","3k","~","Resistor_SMD:R_0603_1608Metric","21","","4006-00300-00"
"R5,R6,R7,R8,R10,R11,R12,R13,R17,R18,R19,R20","249k","~","Resistor_SMD:R_2512_6332Metric","12","","4018-01000-00"
"R9,R14,R21","150","~","Resistor_SMD:R_0603_1608Metric","3","","4006-00040-00"
"R23,R24","4k7","~","Resistor_SMD:R_0603_1608Metric","2","","4006-00150-00"
"R25","1k3","~","Resistor_SMD:R_0603_1608Metric","1","","4006-00130-00"
"R26","1k5","~","Resistor_SMD:R_0603_1608Metric","1","","4006-00140-00"
"R33","47k","~","Resistor_SMD:R_0603_1608Metric","1","DNP","4006-00470-00"
"R34,R51,R52,R53","2k 0.1%","~","Resistor_SMD:R_0603_1608Metric","4","DNP","4006-00200-00"
"R35","1k","~","Resistor_SMD:R_0603_1608Metric","1","","4006-00100-00"
"R44,R45,R46","15k","~","Resistor_SMD:R_0603_1608Metric","3","","4006-00160-00"
"R47","47","~","Resistor_SMD:R_0603_1608Metric","1","","4006-00010-00"
"R71,R72,R73","220","~","Resistor_SMD:R_0603_1608Metric","3","","4006-00020-00"
"RV1,RV2,RV3","MOVS4032V510","~","MOVS4032V510:MOVS4032V460","3","","4022-00010-00"
"TP1","Eticheta","~","Symbol:Eticheta","1","","4000-00000-00"
"U1,U8","AP62250Z6","https://www.diodes.com/assets/Datasheets/AP62250.pdf","Package_TO_SOT_SMD:SOT-563","2","","4520-10010-00"
"U2","ISO3082DW","http://www.ti.com/lit/ds/symlink/iso3082.pdf","Package_SO:SOIC-16W_7.5x10.3mm_P1.27mm","1","","4700-00010-00"
"U3,U12,U13","LM358","http://www.ti.com/lit/ds/symlink/lm2904-n.pdf","Package_SO:SO-8_3.9x4.9mm_P1.27mm","3","","4708-00021-00"
"U4,U6,U7","AMC1400QDWLRQ1","","AMC1400:AMC1400QDWLRQ1","3","","4710-00010-00"
"U5","L78L05ACUTR","http://www.st.com/content/ccc/resource/technical/document/da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","Package_TO_SOT_SMD:SOT-89-3","1","","4522-00010-00"
"U9","74LVC2G157","http://www.ti.com/lit/sg/scyt129e/scyt129e.pdf","Package_SO:VSSOP-8_2.4x2.1mm_P0.5mm","1","","4700-00030-00"
"U11,U20","MAX31865ATP+T","MAX31865ATP+T","MAX31865:21-0140L_T2055-5_MXM","2","DNP","4706-00040-00"
"U14,U15,U16,U17,U18,U19","10061913-100CLF","","PCI_SMD_MOD:10061913-100CLF","6","","4410-00010-00"
"U21","LM2662MX","http://www.ti.com/lit/ds/symlink/lmc7660.pdf","Package_SO:SO-8_3.9x4.9mm_P1.27mm","1","","4520-00020-01"
"U22","MSP430FR2672TRHBR","MSP430FR2672TRHBR","MSP430FR2672TRHBR:VQFN32_5X5_TEX","1","DNP","4704-00020-00"
"Y1","ECS-.327-6-34B-C-TR","~","Crystal:Crystal_SMD_EuroQuartz_EQ161-2Pin_3.2x1.5mm","1","DNP","4714-00010-00"

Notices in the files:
parts and their libraries:
Copyright 2021 Accelerated Designs. All rights reserved.
